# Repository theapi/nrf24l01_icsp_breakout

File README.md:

# nrf_nano
Dev board for Arduino Nano with an MRF24L01
https://arduino-info.wikispaces.com/Nrf24L01-2.4GHz-HowTo

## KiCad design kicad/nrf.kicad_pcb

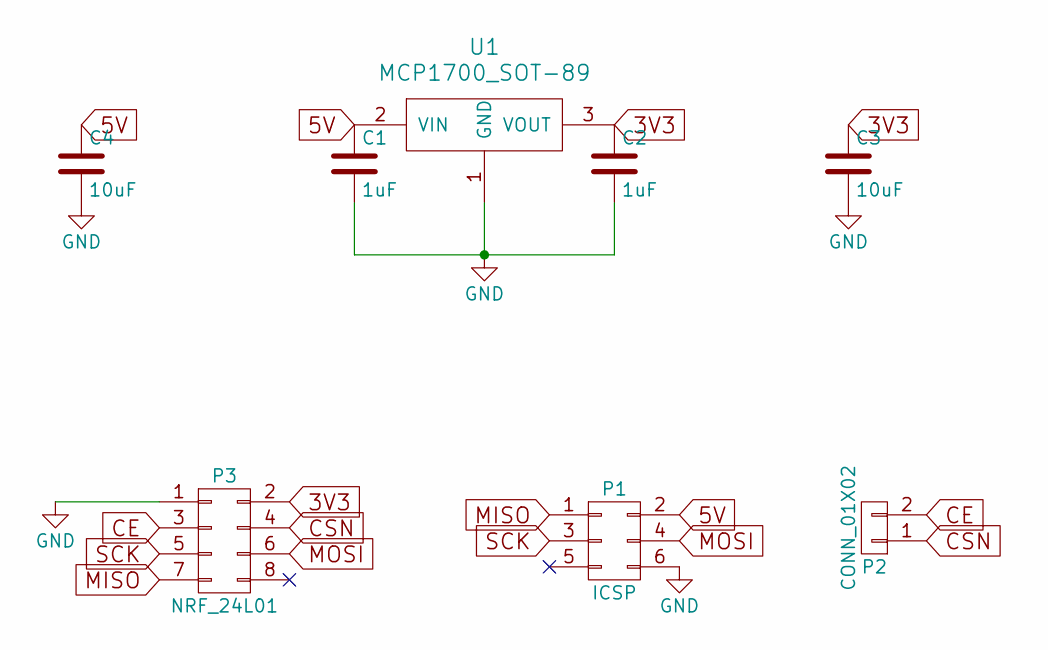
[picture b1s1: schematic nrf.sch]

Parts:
C1, C2: 1uF; C_0805_HandSoldering
C3, C4: 10uF; C_0805_HandSoldering
P1: ICSP; Socket_Strip_Straight_2x03
P2: CONN_01X02; Socket_Strip_Straight_1x02
P3: NRF_24L01
U1: MCP1700_SOT-89; SOT89-3_Housing_Handsoldering

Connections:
3V3: C2.1, C3.1, P3.2, U1.3 (VOUT)
5V: C1.1, C4.1, P1.2, U1.2 (VIN)
CE: P2.2, P3.3
CSN: P2.1, P3.4
GND: C1.2, C2.2, C3.2, C4.2, P1.6, P3.1, U1.1 (GND)
MISO: P1.1, P3.7
MOSI: P1.4, P3.6
SCK: P1.3, P3.5

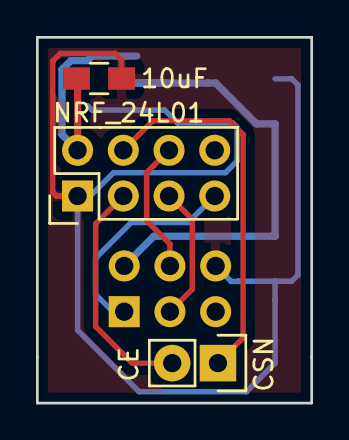
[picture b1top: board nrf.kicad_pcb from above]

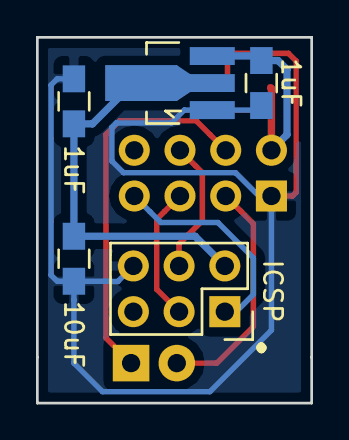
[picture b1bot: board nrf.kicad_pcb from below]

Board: 2 copper layers, 15.2 x 20.3 mm, 8 parts (5 on the bottom side), 8 nets.

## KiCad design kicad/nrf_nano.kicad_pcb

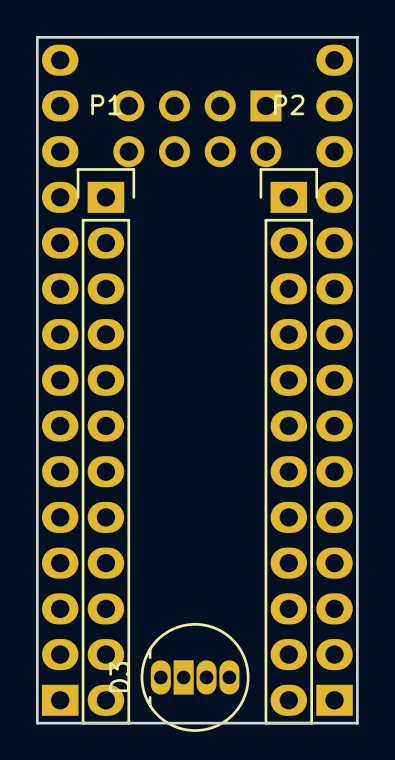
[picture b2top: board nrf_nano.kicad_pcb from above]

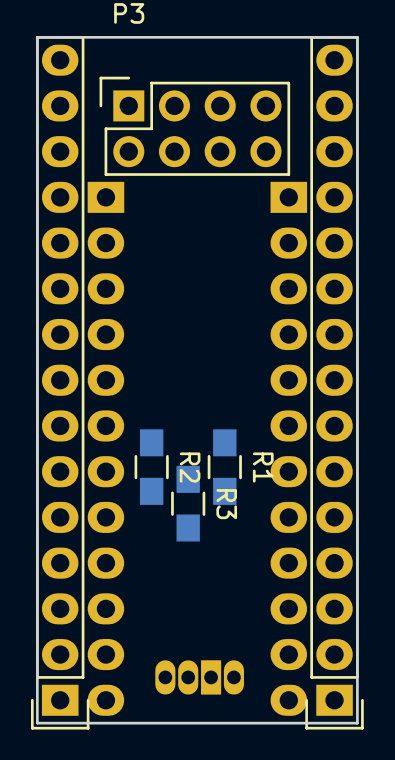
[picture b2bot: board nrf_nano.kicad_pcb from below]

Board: 2 copper layers, 17.8 x 38.1 mm, 9 parts (6 on the bottom side), 13 nets, no tracks yet.

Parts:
D3: LED_RCBG; LED-RGB-5MM_Common_Cathode
P1, P2: CONN_01X12; Pin_Header_Straight_1x12
P3: NRF_24L01; Socket_Strip_Straight_2x04
P4, P6: CONN_01X15; Socket_Strip_Straight_1x15
R1: 180R; R_0805_HandSoldering
R2, R3: 100R; R_0805_HandSoldering

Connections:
3V3: P3.2, P6.2
D3: P4.10, R1.2
D6: P4.7, R2.2
D7: P3.3, P4.6
D8: P3.4, P4.5
D9: P4.4, R3.2
GND: D3.2, P3.1, P4.12, P6.14
MISO: P3.7, P4.1
MOSI: P3.6, P4.2
unnamed: D3.1, R1.1
unnamed: D3.3, R3.1
unnamed: D3.4, R2.1
SCK: P3.5, P6.1

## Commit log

2016-04-26 Initial thoughts
2016-04-26 Small breakout board, initial thoughts
2016-04-27 Voltage regulator
2016-04-27 Traces
2016-05-03 Logo
2016-05-03 gerbers
2016-05-03 gerber zip
